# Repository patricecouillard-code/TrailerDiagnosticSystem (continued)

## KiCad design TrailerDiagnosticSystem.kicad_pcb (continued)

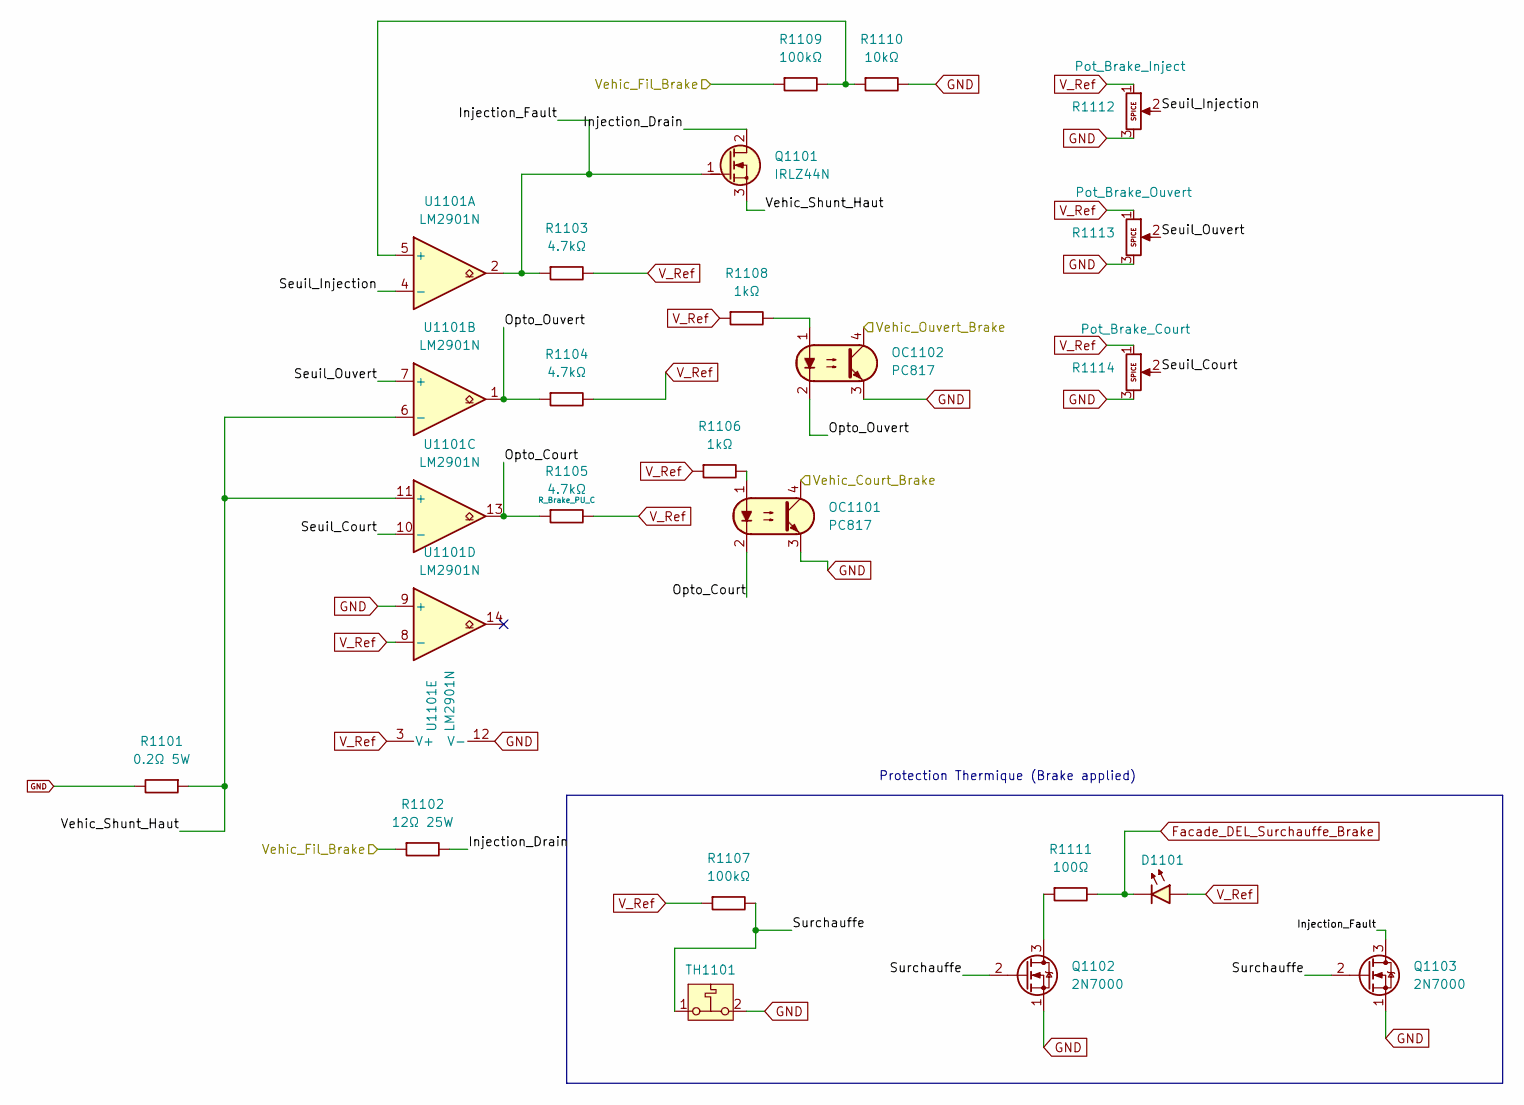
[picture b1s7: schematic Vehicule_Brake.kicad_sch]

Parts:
D1101: RGB 5mm CA (ambre); LED_D5.0mm-4_RGB_Staggered_Pins; MPN WP154A4SEJ3VBDZGW/CA
OC1101, OC1102: PC817; DIP-4_W7.62mm_LongPads
Q1101: IRLZ44N; TO-220-3_Vertical_GDS
Q1102, Q1103: 2N7000; TO-92_Inline_Wide_SGD
R1101: 0.2Ω 5W; R_Axial_Power_L25.0mm_W9.0mm_P27.94mm; MPN SQP500JB-0R2
R1102: 12Ω 25W; TerminalBlock_Phoenix_PT-1,5-2-3.5-H_1x02_P3.50mm_Horizontal; MPN HSA2512RJ
R1103, R1104, R1105: 4.7kΩ; R_Axial_DIN0207_L6.3mm_D2.5mm_P10.16mm_Horizontal
R1106, R1108: 1kΩ; R_Axial_DIN0207_L6.3mm_D2.5mm_P10.16mm_Horizontal
R1107, R1109: 100kΩ; R_Axial_DIN0207_L6.3mm_D2.5mm_P10.16mm_Horizontal
R1110: 10kΩ; R_Axial_DIN0207_L6.3mm_D2.5mm_P10.16mm_Horizontal
R1111: 100Ω; R_Axial_DIN0207_L6.3mm_D2.5mm_P10.16mm_Horizontal
R1112, R1113, R1114: 10kΩ; TRIM_3296W1103LF; MPN 3296W-1-103LF
TH1101: Thermostat 95°C NC; TerminalBlock_Phoenix_PT-1,5-2-3.5-H_1x02_P3.50mm_Horizontal; MPN CS709525Y
U1101: LM2901N; DIP-14_W7.62mm_Socket

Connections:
/Canal_Brake/Bloc_Test_Brake/Vehic_Court_Brake: OC1101.4; also elsewhere on the board
/Canal_Brake/Bloc_Test_Brake/Vehic_Ouvert_Brake: OC1102.4; also elsewhere on the board
/Canal_Brake/Vehicule_Brake/Injection_Drain: Q1101.2 (D), R1102.2
/Canal_Brake/Vehicule_Brake/Injection_Fault: Q1101.1 (G), Q1103.3 (D), R1103.1, U1101.2
/Canal_Brake/Vehicule_Brake/Opto_Court: OC1101.2, R1105.1, U1101.13
/Canal_Brake/Vehicule_Brake/Opto_Ouvert: OC1102.2, R1104.1, U1101.1
/Canal_Brake/Vehicule_Brake/Seuil_Court: R1114.2, U1101.10 (-)
/Canal_Brake/Vehicule_Brake/Seuil_Injection: R1112.2, U1101.4 (-)
/Canal_Brake/Vehicule_Brake/Seuil_Ouvert: R1113.2, U1101.7 (+)
/Canal_Brake/Vehicule_Brake/Surchauffe: Q1102.2 (G), Q1103.2 (G), R1107.2, TH1101.1
/Canal_Brake/Vehicule_Brake/Vehic_Shunt_Haut: Q1101.3 (S), R1101.1, U1101.6 (-), U1101.11 (+)
/Vehic_Fil_Brake: R1102.1, R1109.1; also elsewhere on the board
Facade_DEL_Surchauffe_Brake: D1101.1 (K), R1111.2; also elsewhere on the board
GND: OC1101.3, OC1102.3, Q1102.1 (S), Q1103.1 (S), R1101.2, R1110.2, R1112.3, R1113.3, R1114.3, TH1101.2, U1101.9 (+), U1101.12 (V-); also elsewhere on the board
unnamed: OC1101.1, R1106.2
unnamed: OC1102.1, R1108.2
unnamed: Q1102.3 (D), R1111.1
unnamed: R1109.2, R1110.1, U1101.5 (+)
V_Ref: D1101.2 (A), R1103.2, R1104.2, R1105.2, R1106.1, R1107.1, R1108.1, R1112.1, R1113.1, R1114.1, U1101.3 (V+), U1101.8 (-); also elsewhere on the board

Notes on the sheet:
Protection Thermique (Brake applied)

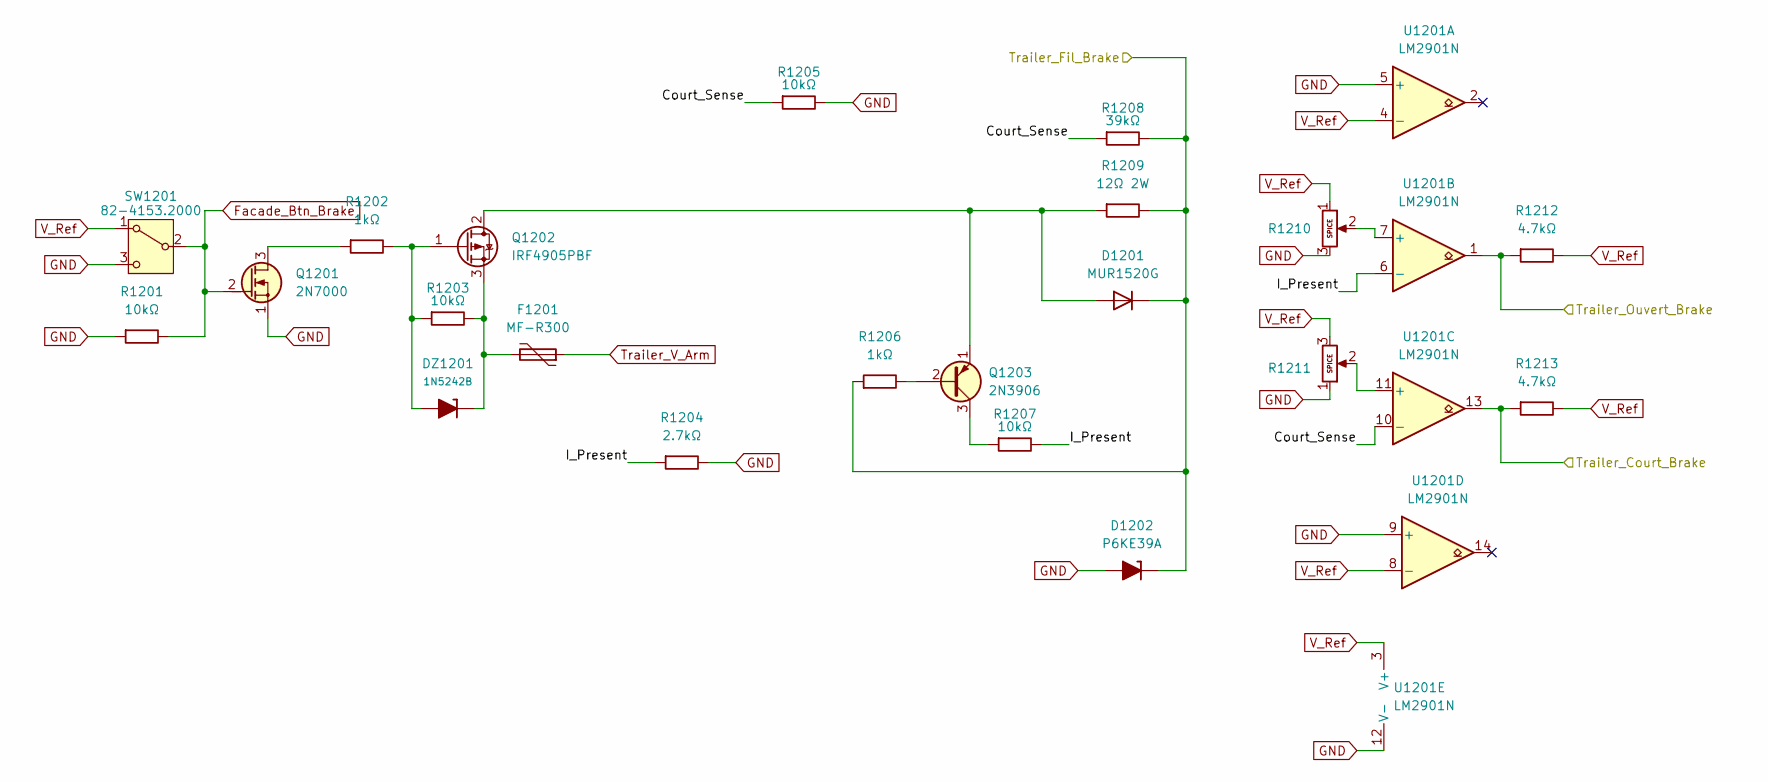
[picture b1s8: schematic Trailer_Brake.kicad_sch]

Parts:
D1201: MUR1520G; TO-220-2_Vertical
D1202: P6KE39A; D_DO-15_P10.16mm_Horizontal_Zener
DZ1201: 1N5242B; D_DO-35_SOD27_P7.62mm_Horizontal_Zener
F1201: MF-R300; PTC_Bourns_MF-R_P5.10mm_W12.0mm
Q1201: 2N7000; TO-92_Inline_Wide_SGD
Q1202: IRF4905PBF; TO-220-3_Vertical
Q1203: 2N3906; TO-92_Inline_Wide_EBC
R1201, R1203, R1205, R1207: 10kΩ; R_Axial_DIN0207_L6.3mm_D2.5mm_P10.16mm_Horizontal
R1202, R1206: 1kΩ; R_Axial_DIN0207_L6.3mm_D2.5mm_P10.16mm_Horizontal
R1204: 2.7kΩ; R_Axial_DIN0207_L6.3mm_D2.5mm_P10.16mm_Horizontal
R1208: 39kΩ; R_Axial_DIN0207_L6.3mm_D2.5mm_P10.16mm_Horizontal
R1209: 12Ω 2W; R_Axial_DIN0414_L11.9mm_D4.5mm_P15.24mm_Horizontal; MPN PR02000201209JR500
R1210, R1211: 10kΩ; TRIM_3296W1103LF; MPN 3296W-1-103LF
R1212, R1213: 4.7kΩ; R_Axial_DIN0207_L6.3mm_D2.5mm_P10.16mm_Horizontal
SW1201: 82-4153.2000
U1201: LM2901N; DIP-14_W7.62mm_Socket

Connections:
/Canal_Brake/Bloc_Test_Brake/Trailer_Court_Brake: R1213.1, U1201.13; also elsewhere on the board
/Canal_Brake/Bloc_Test_Brake/Trailer_Ouvert_Brake: R1212.1, U1201.1; also elsewhere on the board
/Canal_Brake/Trailer_Brake/Court_Sense: R1205.1, R1208.1, U1201.10 (-)
/Canal_Brake/Trailer_Brake/I_Present: R1204.1, R1207.2, U1201.6 (-)
/Trailer_Fil_Brake: D1201.1 (K), D1202.1 (K), R1206.1, R1208.2, R1209.2; also elsewhere on the board
Facade_Btn_Brake: Q1201.2 (G), R1201.2, SW1201.2 (B); also elsewhere on the board
GND: D1202.2 (A), Q1201.1 (S), R1201.1, R1204.2, R1205.2, R1210.3, R1211.1, SW1201.3 (C), U1201.5 (+), U1201.9 (+), U1201.12 (V-); also elsewhere on the board
unnamed: D1201.2 (A), Q1202.2 (D), Q1203.1 (E), R1209.1
unnamed: DZ1201.2 (A), Q1202.1 (G), R1202.2, R1203.1
unnamed: DZ1201.1 (K), F1201.2, Q1202.3 (S), R1203.2
unnamed: Q1201.3 (D), R1202.1
unnamed: Q1203.2 (B), R1206.2
unnamed: Q1203.3 (C), R1207.1
unnamed: R1210.2, U1201.7 (+)
unnamed: R1211.2, U1201.11 (+)
Trailer_V_Arm: F1201.1; also elsewhere on the board
V_Ref: R1210.1, R1211.3, R1212.2, R1213.2, SW1201.1 (A), U1201.3 (V+), U1201.4 (-), U1201.8 (-); also elsewhere on the board

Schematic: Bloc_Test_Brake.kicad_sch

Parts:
D1301, D1302, D1303, D1304, D1305, D1306, D1307, D1308, D1309, D1310, D1311, D1312, D1313, D1314, D1315, D1316, D1317, D1318, D1319, D1320, D1321, D1322, D1323: 1N4148; D_DO-35_SOD27_P7.62mm_Horizontal
D1324: RGB 5mm CA; LED_D5.0mm-4_RGB_Staggered_Pins; MPN WP154A4SEJ3VBDZGW/CA
Q1301, Q1302, Q1303, Q1304, Q1305, Q1306: 2N7000; TO-92_Inline_Wide_SGD
R1301, R1302, R1304, R1306, R1307, R1309, R1315: 4.7kΩ; R_Axial_DIN0207_L6.3mm_D2.5mm_P10.16mm_Horizontal
R1303, R1305: 100kΩ; R_Axial_DIN0207_L6.3mm_D2.5mm_P10.16mm_Horizontal
R1308, R1311, R1312: 470kΩ; R_Axial_DIN0207_L6.3mm_D2.5mm_P10.16mm_Horizontal
R1310: 150Ω; R_Axial_DIN0207_L6.3mm_D2.5mm_P10.16mm_Horizontal
R1313: 470Ω; R_Axial_DIN0207_L6.3mm_D2.5mm_P10.16mm_Horizontal
R1314: 680Ω; R_Axial_DIN0207_L6.3mm_D2.5mm_P10.16mm_Horizontal

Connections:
/Canal_Brake/Bloc_Test_Brake/Bleu: D1307.2 (A), D1308.2 (A), D1317.2 (A), D1320.2 (A), R1304.1
/Canal_Brake/Bloc_Test_Brake/Court: D1305.1 (K), D1306.1 (K), D1319.2 (A), D1321.2 (A), Q1302.2 (G), R1303.1
/Canal_Brake/Bloc_Test_Brake/Fault_Actif: D1319.1 (K), D1320.1 (K), D1323.1 (K), Q1304.2 (G), R1311.1
/Canal_Brake/Bloc_Test_Brake/Not_Btn: D1308.1 (K), Q1303.3 (D), R1309.2
/Canal_Brake/Bloc_Test_Brake/Ouvert: D1309.1 (K), D1310.1 (K), D1316.2 (A), D1322.2 (A), D1323.2 (A), R1305.2
/Canal_Brake/Bloc_Test_Brake/Ouvert_Ou_Bleu: D1316.1 (K), D1317.1 (K), Q1301.2 (G), Q1302.3 (D), R1308.1
/Canal_Brake/Bloc_Test_Brake/Trailer_Court_Actif: D1306.2 (A), D1314.2 (A), D1315.2 (A), D1318.2 (A), R1306.1
/Canal_Brake/Bloc_Test_Brake/Trailer_Court_Brake: D1314.1 (K); also elsewhere on the board
/Canal_Brake/Bloc_Test_Brake/Trailer_Ouvert_Actif: D1310.2 (A), D1311.2 (A), D1312.2 (A), D1313.2 (A), R1307.1
/Canal_Brake/Bloc_Test_Brake/Trailer_Ouvert_Brake: D1311.1 (K); also elsewhere on the board
/Canal_Brake/Bloc_Test_Brake/Vehic_Court_Actif: D1303.2 (A), D1304.2 (A), D1305.2 (A), R1302.1
/Canal_Brake/Bloc_Test_Brake/Vehic_Court_Brake: D1303.1 (K); also elsewhere on the board
/Canal_Brake/Bloc_Test_Brake/Vehic_Ouvert_Actif: D1301.2 (A), D1302.2 (A), D1309.2 (A), R1301.1
/Canal_Brake/Bloc_Test_Brake/Vehic_Ouvert_Brake: D1301.1 (K); also elsewhere on the board
/Canal_Brake/Bloc_Test_Brake/Vert_Enable: Q1304.3 (D), Q1305.2 (G), R1315.2
Facade_Brake_B: D1324.3 (BK), R1310.2; also elsewhere on the board
Facade_Brake_G: D1324.4 (GK), R1313.2; also elsewhere on the board
Facade_Brake_R: D1324.1 (RK), R1314.2; also elsewhere on the board
Facade_Btn_Brake: D1313.1 (K), D1318.1 (K), Q1303.2 (G); also elsewhere on the board
GND: Q1301.1 (S), Q1302.1 (S), Q1303.1 (S), Q1304.1 (S), Q1305.1 (S), Q1306.1 (S), R1303.2, R1305.1, R1308.2, R1311.2, R1312.1; also elsewhere on the board
Mode_Trailer: D1307.1 (K), D1312.1 (K), D1315.1 (K); also elsewhere on the board
Mode_Vehic: D1302.1 (K), D1304.1 (K); also elsewhere on the board
unnamed: D1321.1 (K), D1322.1 (K), Q1306.2 (G), R1312.2
unnamed: Q1301.3 (D), R1310.1
unnamed: Q1305.3 (D), R1313.1
unnamed: Q1306.3 (D), R1314.1
V_Ref: D1324.2 (A), R1301.2, R1302.2, R1304.2, R1306.2, R1307.2, R1309.1, R1315.1; also elsewhere on the board

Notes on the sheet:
Ouvert_V_Actif (Porte ET #3)
Court_V_Actif (Porte ET #1)
Court_T_Actif (Porte ET #2)
Rouge_Enable
Inverseur de bouton (Noeud not_btn_tail)
Court_Brake (Porte OU #1)
Ouvert_T_Actif_Brake (Porte ET #4 - 3 entrées)
Ouvert_Ou_Bleu
Ouvet_Brake (Porte OU #2)
Porte ET #5 (Bleu_Brake)

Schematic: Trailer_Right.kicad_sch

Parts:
D2001: MUR1520G; TO-220-2_Vertical
D2002: P6KE39A; D_DO-15_P10.16mm_Horizontal_Zener
DZ2001: 1N5242B; D_DO-35_SOD27_P7.62mm_Horizontal_Zener
F2001: MF-R700; PTC_Bourns_MF-R_P10.20mm_W24.2mm
Q2001: 2N7000; TO-92_Inline_Wide_SGD
Q2002: IRF4905PBF; TO-220-3_Vertical
Q2003: 2N3906; TO-92_Inline_Wide_EBC
R2001, R2003, R2005, R2007: 10kΩ; R_Axial_DIN0207_L6.3mm_D2.5mm_P10.16mm_Horizontal
R2002, R2006: 1kΩ; R_Axial_DIN0207_L6.3mm_D2.5mm_P10.16mm_Horizontal
R2004: 2.7kΩ; R_Axial_DIN0207_L6.3mm_D2.5mm_P10.16mm_Horizontal
R2008: 39kΩ; R_Axial_DIN0207_L6.3mm_D2.5mm_P10.16mm_Horizontal
R2009: 12Ω 2W; R_Axial_DIN0414_L11.9mm_D4.5mm_P15.24mm_Horizontal; MPN PR02000201209JR500
R2010, R2011: 10kΩ; TRIM_3296W1103LF; MPN 3296W-1-103LF
R2012, R2013: 4.7kΩ; R_Axial_DIN0207_L6.3mm_D2.5mm_P10.16mm_Horizontal
SW2001: 82-4153.2000
U2001: LM2901N; DIP-14_W7.62mm_Socket

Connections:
/Canal_Right/Bloc_Test_Right/Trailer_Court_Right: R2013.1, U2001.13; also elsewhere on the board
/Canal_Right/Bloc_Test_Right/Trailer_Ouvert_Right: R2012.1, U2001.1; also elsewhere on the board
/Canal_Right/Trailer_Right/Court_Sense: R2005.1, R2008.1, U2001.10 (-)
/Canal_Right/Trailer_Right/I_Present: R2004.1, R2007.2, U2001.6 (-)
/Trailer_Fil_Right: D2001.1 (K), D2002.1 (K), R2006.1, R2008.2, R2009.2; also elsewhere on the board
Facade_Btn_Right: Q2001.2 (G), R2001.2, SW2001.2 (B); also elsewhere on the board
GND: D2002.2 (A), Q2001.1 (S), R2001.1, R2004.2, R2005.2, R2010.3, R2011.1, SW2001.3 (C), U2001.5 (+), U2001.9 (+), U2001.12 (V-); also elsewhere on the board
unnamed: D2001.2 (A), Q2002.2 (D), Q2003.1 (E), R2009.1
unnamed: DZ2001.2 (A), Q2002.1 (G), R2002.2, R2003.1
unnamed: DZ2001.1 (K), F2001.2, Q2002.3 (S), R2003.2
unnamed: Q2001.3 (D), R2002.1
unnamed: Q2003.2 (B), R2006.2
unnamed: Q2003.3 (C), R2007.1
unnamed: R2010.2, U2001.7 (+)
unnamed: R2011.2, U2001.11 (+)
Trailer_V_Arm: F2001.1; also elsewhere on the board
V_Ref: R2010.1, R2011.3, R2012.2, R2013.2, SW2001.1 (A), U2001.3 (V+), U2001.4 (-), U2001.8 (-); also elsewhere on the board

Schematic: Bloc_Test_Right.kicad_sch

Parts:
D2101, D2102, D2103, D2104, D2105, D2106, D2107, D2108, D2109, D2110, D2111, D2112, D2113, D2114, D2115, D2116, D2117, D2118, D2119, D2120, D2121, D2122, D2123: 1N4148; D_DO-35_SOD27_P7.62mm_Horizontal
D2124: RGB 5mm CA; LED_D5.0mm-4_RGB_Staggered_Pins; MPN WP154A4SEJ3VBDZGW/CA
Q2101, Q2102, Q2103, Q2104, Q2105, Q2106: 2N7000; TO-92_Inline_Wide_SGD
R2101, R2104, R2107, R2108, R2110, R2111, R2112: 4.7kΩ; R_Axial_DIN0207_L6.3mm_D2.5mm_P10.16mm_Horizontal
R2102, R2105, R2109: 470kΩ; R_Axial_DIN0207_L6.3mm_D2.5mm_P10.16mm_Horizontal
R2103, R2106: 100kΩ; R_Axial_DIN0207_L6.3mm_D2.5mm_P10.16mm_Horizontal
R2113: 680Ω; R_Axial_DIN0207_L6.3mm_D2.5mm_P10.16mm_Horizontal
R2114: 470Ω; R_Axial_DIN0207_L6.3mm_D2.5mm_P10.16mm_Horizontal
R2115: 150Ω; R_Axial_DIN0207_L6.3mm_D2.5mm_P10.16mm_Horizontal

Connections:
/Canal_Right/Bloc_Test_Right/Bleu: D2104.2 (A), D2113.2 (A), D2122.2 (A), D2123.2 (A), R2112.1
/Canal_Right/Bloc_Test_Right/Court: D2109.1 (K), D2110.1 (K), D2111.2 (A), D2117.2 (A), Q2101.2 (G), R2106.2
/Canal_Right/Bloc_Test_Right/Fault_Actif: D2111.1 (K), D2112.1 (K), D2113.1 (K), Q2102.2 (G), R2105.1
/Canal_Right/Bloc_Test_Right/Not_Btn: D2123.1 (K), Q2103.3 (D), R2111.2
/Canal_Right/Bloc_Test_Right/Ouvert: D2103.2 (A), D2105.1 (K), D2106.1 (K), D2112.2 (A), D2118.2 (A), R2103.2
/Canal_Right/Bloc_Test_Right/Ouvert_Ou_Bleu: D2103.1 (K), D2104.1 (K), Q2101.3 (D), Q2106.2 (G), R2102.2
/Canal_Right/Bloc_Test_Right/Rouge_Enable: D2117.1 (K), D2118.1 (K), Q2104.2 (G), R2109.2
/Canal_Right/Bloc_Test_Right/Trailer_Court_Actif: D2107.2 (A), D2108.2 (A), D2110.2 (A), D2116.2 (A), R2104.1
/Canal_Right/Bloc_Test_Right/Trailer_Court_Right: D2107.1 (K); also elsewhere on the board
/Canal_Right/Bloc_Test_Right/Trailer_Ouvert_Actif: D2106.2 (A), D2119.2 (A), D2120.2 (A), D2121.2 (A), R2110.1
/Canal_Right/Bloc_Test_Right/Trailer_Ouvert_Right: D2119.1 (K); also elsewhere on the board
/Canal_Right/Bloc_Test_Right/Vehic_Court_Actif: D2101.2 (A), D2102.2 (A), D2109.2 (A), R2101.1
/Canal_Right/Bloc_Test_Right/Vehic_Court_Right: D2101.1 (K); also elsewhere on the board
/Canal_Right/Bloc_Test_Right/Vehic_Ouvert_Actif: D2105.2 (A), D2114.2 (A), D2115.2 (A), R2108.1
/Canal_Right/Bloc_Test_Right/Vehic_Ouvert_Right: D2114.1 (K); also elsewhere on the board
/Canal_Right/Bloc_Test_Right/Vert_Enable: Q2102.3 (D), Q2105.2 (G), R2107.2
Facade_Btn_Right: D2116.1 (K), D2121.1 (K), Q2103.2 (G); also elsewhere on the board
Facade_Right_B: D2124.3 (BK), R2115.2; also elsewhere on the board
Facade_Right_G: D2124.4 (GK), R2114.2; also elsewhere on the board
Facade_Right_R: D2124.1 (RK), R2113.2; also elsewhere on the board
GND: Q2101.1 (S), Q2102.1 (S), Q2103.1 (S), Q2104.1 (S), Q2105.1 (S), Q2106.1 (S), R2102.1, R2103.1, R2105.2, R2106.1, R2109.1; also elsewhere on the board
Mode_Trailer: D2108.1 (K), D2120.1 (K), D2122.1 (K); also elsewhere on the board
Mode_Vehic: D2102.1 (K), D2115.1 (K); also elsewhere on the board
unnamed: Q2104.3 (D), R2113.1
unnamed: Q2105.3 (D), R2114.1
unnamed: Q2106.3 (D), R2115.1
V_Ref: D2124.2 (A), R2101.2, R2104.2, R2107.1, R2108.2, R2110.2, R2111.1, R2112.2; also elsewhere on the board

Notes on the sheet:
========================================================================== NIVEAU 1 ==========================================================================
Porte OU Fault_Actif_Right (3 entrées) + inverseur vert
3ième Porte "ET" (Ouvert_V_Actif_Right)
=========================================== NIVEAU 2 =================================================
1ère Porte "OU" (Ouvert_Right)
2ième Porte "OU" (Court_Right)
1ère Porte "ET" (Court_V_Actif_Right)
Porte OU Rouge_Enable_Right
4ième Porte "ET" (Ouvert_T_Actif_Right)
Inverseur (Dépendance de Bleu_Right)
2ième Porte "ET" (Court_T_Actif_Right)
5ième Porte "ET" (Bleu_Right)
====================================== NIVEAU 3 ==================
Porte OU Ouvert_Ou_Bleu_Right + override

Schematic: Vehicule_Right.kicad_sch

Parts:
OC1901, OC1902: PC817; DIP-4_W7.62mm_LongPads
Q1901: IRLZ44N; TO-220-3_Vertical_GDS
R1901: 12Ω 25W; TerminalBlock_Phoenix_PT-1,5-2-3.5-H_1x02_P3.50mm_Horizontal; MPN HSA2512RJ
R1902: 0.2Ω 5W; R_Axial_Power_L25.0mm_W9.0mm_P27.94mm; MPN SQP500JB-0R2
R1903, R1904, R1905: 4.7kΩ; R_Axial_DIN0207_L6.3mm_D2.5mm_P10.16mm_Horizontal
R1906, R1907: 1kΩ; R_Axial_DIN0207_L6.3mm_D2.5mm_P10.16mm_Horizontal
R1908: 100kΩ; R_Axial_DIN0207_L6.3mm_D2.5mm_P10.16mm_Horizontal
R1909: 10kΩ; R_Axial_DIN0207_L6.3mm_D2.5mm_P10.16mm_Horizontal
R1910, R1911, R1912: 10kΩ; TRIM_3296W1103LF; MPN 3296W-1-103LF
U1901: LM2901N; DIP-14_W7.62mm_Socket

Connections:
/Canal_Right/Bloc_Test_Right/Vehic_Court_Right: OC1901.4; also elsewhere on the board
/Canal_Right/Bloc_Test_Right/Vehic_Ouvert_Right: OC1902.4; also elsewhere on the board
/Canal_Right/Vehicule_Right/Injection_Drain: Q1901.2 (D), R1901.2
/Canal_Right/Vehicule_Right/Injection_Fault: Q1901.1 (G), R1903.1, U1901.2
/Canal_Right/Vehicule_Right/Opto_Court: OC1901.2, R1905.1, U1901.13
/Canal_Right/Vehicule_Right/Opto_Ouvert: OC1902.2, R1904.1, U1901.1
/Canal_Right/Vehicule_Right/Seuil_Court: R1912.2, U1901.10 (-)
/Canal_Right/Vehicule_Right/Seuil_Injection: R1910.2, U1901.4 (-)
/Canal_Right/Vehicule_Right/Seuil_Ouvert: R1911.2, U1901.7 (+)
/Canal_Right/Vehicule_Right/Vehic_Shunt_Haut: Q1901.3 (S), R1902.1, U1901.6 (-), U1901.11 (+)
/Vehic_Fil_Right: R1901.1, R1908.1; also elsewhere on the board
GND: OC1901.3, OC1902.3, R1902.2, R1909.2, R1910.3, R1911.3, R1912.3, U1901.9 (+), U1901.12 (V-); also elsewhere on the board
unnamed: OC1901.1, R1906.2
unnamed: OC1902.1, R1907.2
unnamed: R1908.2, R1909.1, U1901.5 (+)
V_Ref: R1903.2, R1904.2, R1905.2, R1906.1, R1907.1, R1910.1, R1911.1, R1912.1, U1901.3 (V+), U1901.8 (-); also elsewhere on the board

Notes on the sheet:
Non_Utilisé
Court-circuit
Ouvvert
Right_Vehic_Shunt_Haut
Injection

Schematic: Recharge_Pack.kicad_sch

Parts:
C401: 2.2µF 50V; CAPRB500W50L450T300H550; MPN FG24X7R1H225KRT06
D401: RGB 5mm CA (bleu); MPN WP154A4SEJ3VBDZGW/CA
J401: EN3P2MX
J402: Micro-Fit 3.0 1x06; Molex_Micro-Fit_3.0_43650-0615_1x06_P3.00mm_Vertical
Q401: IRLZ44N; TO-220-3_Vertical_GDS
R401: 470Ω 1W; R_Axial_DIN0309_L9.0mm_D3.2mm_P12.70mm_Horizontal; MPN PR01000104700JR500
R402: 330Ω; R_Axial_DIN0207_L6.3mm_D2.5mm_P10.16mm_Horizontal
TH401: Thermostat NO 15°C; MPN CS701515Y
U401: LM74610QDGKRQ1; SOP65P490X110-8N; PARTREV B

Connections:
/Alimentation/Batt_Interne_Pos: Q401.2 (D), U401.8 (CATHODE); also elsewhere on the board
/Alimentation/Batt_Neg: J401.2, J402.2, R401.1; also elsewhere on the board
/Alimentation/Recharge_Pack/Recharge_DEL_A: D401.2 (A), J402.5, R402.2
/Alimentation/Recharge_Pack/Recharge_Pos: J401.1, J402.1, J402.3, R402.1, TH401.1 (A)
/Alimentation/Recharge_Pack/Recharge_Therm: D401.1 (K), J402.4, J402.6, Q401.3 (S), R401.2, TH401.2 (B), U401.4 (ANODE)
unnamed: Q401.1 (G), U401.2 (GATE_PULL_DOWN), U401.6 (GATE_DRIVE)
unnamed: C401.1, U401.7 (VCAPH)
unnamed: C401.2, U401.1 (VCAPL)

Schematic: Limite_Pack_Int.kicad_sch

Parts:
C301: 4.7µF 63V; C_Rect_L19.0mm_W7.0mm_P15.00mm_MKS4; MPN MKS4C044704D00KSSD 10%
C302, C303: 10nF 50V; CAPRR254W50L508T317H508; MPN C315C103K5R5TA
D301: RGB 5mm CA (ambre); LED_D5.0mm-4_RGB_Staggered_Pins; MPN WP154A4SEJ3VBDZGW/CA
Q301, Q303: 2N3906; TO-92_Inline_Wide_EBC
Q302: 2N3904; TO-92_Inline_Wide_EBC
Q304: 2N7000; TO-92_Inline_Wide_SGD
R301: 1.5kΩ; R_Axial_DIN0207_L6.3mm_D2.5mm_P10.16mm_Horizontal
R302, R303, R309, R312: 100kΩ; R_Axial_DIN0207_L6.3mm_D2.5mm_P10.16mm_Horizontal
R304: 1kΩ; TRIM_3296W-1-102LF; MPN 3296W-1-102LF
R305: 1kΩ; R_Axial_DIN0207_L6.3mm_D2.5mm_P10.16mm_Horizontal
R306: 18kΩ; R_Axial_DIN0207_L6.3mm_D2.5mm_P10.16mm_Horizontal
R307: 39kΩ; R_Axial_DIN0207_L6.3mm_D2.5mm_P10.16mm_Horizontal
R308, R310: 10kΩ; R_Axial_DIN0207_L6.3mm_D2.5mm_P10.16mm_Horizontal
R311: 1.8kΩ; R_Axial_DIN0207_L6.3mm_D2.5mm_P10.16mm_Horizontal

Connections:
/Alimentation/Batt_Interne_Pos: Q301.1 (E), R301.1; also elsewhere on the board
/Alimentation/Batt_Interne_Shunt: R304.3; also elsewhere on the board
/Alimentation/Bus_CutOff_Gate: Q304.3 (D); also elsewhere on the board
/Alimentation/Limite_Pack_Int/Batt_Ext_Requise: Q303.3 (C), R307.2, R310.1, R311.1
/Alimentation/Limite_Pack_Int/Mesure_Courant_Pack: Q301.2 (B), R305.2
/Alimentation/V_Int_Actif: C303.2, Q303.1 (E), R309.2; also elsewhere on the board
Facade_DEL_Batt_Ext: D301.2 (A), R311.2; also elsewhere on the board
GND: C301.2, C302.1, D301.1 (K), Q302.1 (E), Q304.1 (S), R306.2, R312.2; also elsewhere on the board
unnamed: C301.1, R302.2, R303.1
unnamed: Q301.3 (C), R302.1
unnamed: C302.2, Q302.2 (B), R303.2, R306.1, R307.1
unnamed: Q302.3 (C), R308.1
unnamed: C303.1, Q303.2 (B), R308.2, R309.1
unnamed: Q304.2 (G), R310.2, R312.1
unnamed: R301.2, R304.1
unnamed: R304.2, R305.1

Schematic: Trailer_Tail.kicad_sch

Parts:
D801: MUR1520G; TO-220-2_Vertical
D802: P6KE39A; D_DO-15_P10.16mm_Horizontal_Zener
DZ801: 1N5242B; D_DO-35_SOD27_P7.62mm_Horizontal_Zener
F801: MF-R800; PTC_Bourns_MF-R_P10.20mm_W24.2mm
Q801: 2N7000; TO-92_Inline_Wide_SGD
Q802: IRF4905PBF; TO-220-3_Vertical
Q803: 2N3906; TO-92_Inline_Wide_EBC
R801, R803, R805, R807: 10kΩ; R_Axial_DIN0207_L6.3mm_D2.5mm_P10.16mm_Horizontal
R802, R806: 1kΩ; R_Axial_DIN0207_L6.3mm_D2.5mm_P10.16mm_Horizontal
R804: 2.7kΩ; R_Axial_DIN0207_L6.3mm_D2.5mm_P10.16mm_Horizontal
R808: 39kΩ; R_Axial_DIN0207_L6.3mm_D2.5mm_P10.16mm_Horizontal
R809: 12Ω 2W; R_Axial_DIN0414_L11.9mm_D4.5mm_P15.24mm_Horizontal; MPN PR02000201209JR500
R810, R811: 10kΩ; TRIM_3296W1103LF; MPN 3296W-1-103LF
R812, R813: 4.7kΩ; R_Axial_DIN0207_L6.3mm_D2.5mm_P10.16mm_Horizontal
SW801: 82-4153.2000
U801: LM2901N; DIP-14_W7.62mm_Socket

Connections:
/Canal_Tail/Bloc_Test_Tail/Trailer_Court_Tail: R813.1, U801.13; also elsewhere on the board
/Canal_Tail/Bloc_Test_Tail/Trailer_Ouvert_Tail: R812.1, U801.1; also elsewhere on the board
/Canal_Tail/Trailer_Tail/Court_Sense: R805.1, R808.1, U801.10 (-)
/Canal_Tail/Trailer_Tail/I_Present: R804.1, R807.2, U801.6 (-)
/Trailer_Fil_Tail: D801.1 (K), D802.1 (K), R806.1, R808.2, R809.2; also elsewhere on the board
Facade_Btn_Tail: Q801.2 (G), R801.2, SW801.2 (B); also elsewhere on the board
GND: D802.2 (A), Q801.1 (S), R801.1, R804.2, R805.2, R810.3, R811.1, SW801.3 (C), U801.5 (+), U801.9 (+), U801.12 (V-); also elsewhere on the board
unnamed: D801.2 (A), Q802.2 (D), Q803.1 (E), R809.1
unnamed: DZ801.2 (A), Q802.1 (G), R802.2, R803.1
unnamed: DZ801.1 (K), F801.2, Q802.3 (S), R803.2
unnamed: Q801.3 (D), R802.1
unnamed: Q803.2 (B), R806.2
unnamed: Q803.3 (C), R807.1
unnamed: R810.2, U801.7 (+)
unnamed: R811.2, U801.11 (+)
Trailer_V_Arm: F801.1; also elsewhere on the board
V_Ref: R810.1, R811.3, R812.2, R813.2, SW801.1 (A), U801.3 (V+), U801.4 (-), U801.8 (-); also elsewhere on the board

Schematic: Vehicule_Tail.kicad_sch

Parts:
OC701, OC702: PC817; DIP-4_W7.62mm_LongPads
Q701: IRLZ44N; TO-220-3_Vertical_GDS
R701: 12Ω 25W; TerminalBlock_Phoenix_PT-1,5-2-3.5-H_1x02_P3.50mm_Horizontal; MPN HSA2512RJ
R702: 0.2Ω 5W; R_Axial_Power_L25.0mm_W9.0mm_P27.94mm; MPN SQP500JB-0R2
R703, R704, R705: 4.7kΩ; R_Axial_DIN0207_L6.3mm_D2.5mm_P10.16mm_Horizontal
R706, R707: 1kΩ; R_Axial_DIN0207_L6.3mm_D2.5mm_P10.16mm_Horizontal
R708: 100kΩ; R_Axial_DIN0207_L6.3mm_D2.5mm_P10.16mm_Horizontal
R709: 10kΩ; R_Axial_DIN0207_L6.3mm_D2.5mm_P10.16mm_Horizontal
R710, R711, R712: 10kΩ; TRIM_3296W1103LF; MPN 3296W-1-103LF
U701: LM2901N; DIP-14_W7.62mm_Socket

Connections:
/Canal_Tail/Bloc_Test_Tail/Vehic_Court_Tail: OC701.4; also elsewhere on the board
/Canal_Tail/Bloc_Test_Tail/Vehic_Ouvert_Tail: OC702.4; also elsewhere on the board
/Canal_Tail/Vehicule_Tail/Injection_Drain: Q701.2 (D), R701.2
/Canal_Tail/Vehicule_Tail/Injection_Fault: Q701.1 (G), R703.1, U701.2
/Canal_Tail/Vehicule_Tail/Seuil_Court: R712.2, U701.10 (-)
/Canal_Tail/Vehicule_Tail/Seuil_Injection: R710.2, U701.4 (-)
/Canal_Tail/Vehicule_Tail/Seuil_Ouvert: R711.2, U701.7 (+)
/Canal_Tail/Vehicule_Tail/Vehic_Shunt_Haut: Q701.3 (S), R702.1, U701.6 (-), U701.11 (+)
/Vehic_Fil_Tail: R701.1, R708.1; also elsewhere on the board
GND: OC701.3, OC702.3, R702.2, R709.2, R710.3, R711.3, R712.3, U701.9 (+), U701.12 (V-); also elsewhere on the board
unnamed: OC701.1, R706.2
unnamed: OC701.2, R705.1, U701.13
unnamed: OC702.1, R707.2
unnamed: OC702.2, R704.1, U701.1
unnamed: R708.2, R709.1, U701.5 (+)
V_Ref: R703.2, R704.2, R705.2, R706.1, R707.1, R710.1, R711.1, R712.1, U701.3 (V+), U701.8 (-); also elsewhere on the board

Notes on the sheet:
Injection
Ouvvert
Court-circuit
Non_Utilisé

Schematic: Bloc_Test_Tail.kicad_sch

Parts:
D901, D902, D903, D904, D905, D906, D907, D908, D909, D910, D911, D912, D913, D914, D915, D916, D917, D918, D919, D920, D921, D922, D923: 1N4148; D_DO-35_SOD27_P7.62mm_Horizontal
D924: RGB 5mm CA; LED_D5.0mm-4_RGB_Staggered_Pins; MPN WP154A4SEJ3VBDZGW/CA
Q901, Q902, Q903, Q904, Q905, Q906: 2N7000; TO-92_Inline_Wide_SGD
R901, R902, R904, R905, R906, R909, R915: 4.7kΩ; R_Axial_DIN0207_L6.3mm_D2.5mm_P10.16mm_Horizontal
R903, R907: 100kΩ; R_Axial_DIN0207_L6.3mm_D2.5mm_P10.16mm_Horizontal
R908, R911, R913: 470kΩ; R_Axial_DIN0207_L6.3mm_D2.5mm_P10.16mm_Horizontal
R910: 150Ω; R_Axial_DIN0207_L6.3mm_D2.5mm_P10.16mm_Horizontal
R912: 470Ω; R_Axial_DIN0207_L6.3mm_D2.5mm_P10.16mm_Horizontal
R914: 680Ω; R_Axial_DIN0207_L6.3mm_D2.5mm_P10.16mm_Horizontal

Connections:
/Canal_Tail/Bloc_Test_Tail/Bleu: D907.2 (A), D908.2 (A), D918.2 (A), D920.2 (A), R904.1
/Canal_Tail/Bloc_Test_Tail/Court: D905.1 (K), D906.1 (K), D919.2 (A), D921.2 (A), Q902.2 (G), R903.1
/Canal_Tail/Bloc_Test_Tail/Fault_Actif: D919.1 (K), D920.1 (K), D923.1 (K), Q905.2 (G), R911.1
/Canal_Tail/Bloc_Test_Tail/Not_Btn: D908.1 (K), Q903.3 (D), R909.2
/Canal_Tail/Bloc_Test_Tail/Ouvert: D915.1 (K), D916.1 (K), D917.2 (A), D922.2 (A), D923.2 (A), R907.2
/Canal_Tail/Bloc_Test_Tail/Ouvert_Ou_Bleu: D917.1 (K), D918.1 (K), Q901.2 (G), Q902.3 (D), R908.1
/Canal_Tail/Bloc_Test_Tail/Trailer_Court_Actif: D906.2 (A), D912.2 (A), D913.2 (A), D914.2 (A), R906.1
/Canal_Tail/Bloc_Test_Tail/Trailer_Court_Tail: D912.1 (K); also elsewhere on the board
/Canal_Tail/Bloc_Test_Tail/Trailer_Ouvert_Actif: D909.2 (A), D910.2 (A), D911.2 (A), D916.2 (A), R905.1
/Canal_Tail/Bloc_Test_Tail/Trailer_Ouvert_Tail: D909.1 (K); also elsewhere on the board
/Canal_Tail/Bloc_Test_Tail/Vehic_Court_Actif: D903.2 (A), D904.2 (A), D905.2 (A), R902.1
/Canal_Tail/Bloc_Test_Tail/Vehic_Court_Tail: D903.1 (K); also elsewhere on the board
/Canal_Tail/Bloc_Test_Tail/Vehic_Ouvert_Actif: D901.2 (A), D902.2 (A), D915.2 (A), R901.1
/Canal_Tail/Bloc_Test_Tail/Vehic_Ouvert_Tail: D901.1 (K); also elsewhere on the board
/Canal_Tail/Bloc_Test_Tail/Vert_Enable: Q904.2 (G), Q905.3 (D), R915.2
Facade_Btn_Tail: D911.1 (K), D914.1 (K), Q903.2 (G); also elsewhere on the board
Facade_Tail_B: D924.3 (BK), R910.2; also elsewhere on the board
Facade_Tail_G: D924.4 (GK), R912.2; also elsewhere on the board
Facade_Tail_R: D924.1 (RK), R914.2; also elsewhere on the board
GND: Q901.1 (S), Q902.1 (S), Q903.1 (S), Q904.1 (S), Q905.1 (S), Q906.1 (S), R903.2, R907.1, R908.2, R911.2, R913.1; also elsewhere on the board
Mode_Trailer: D907.1 (K), D910.1 (K), D913.1 (K); also elsewhere on the board
Mode_Vehic: D902.1 (K), D904.1 (K); also elsewhere on the board
unnamed: D921.1 (K), D922.1 (K), Q906.2 (G), R913.2
unnamed: Q901.3 (D), R910.1
unnamed: Q904.3 (D), R912.1
unnamed: Q906.3 (D), R914.1
V_Ref: D924.2 (A), R901.2, R902.2, R904.2, R905.2, R906.2, R909.1, R915.1; also elsewhere on the board

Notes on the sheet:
Ouvert_V_Actif (Porte ET #3)
Ouvert_Ou_Bleu
Court_T_Actif (Porte ET #2)
Ouvet_Tail (Porte OU #2)
Ouvert_T_Actif (Porte ET #4 - 3 entrées)
Court_Tail (Porte OU #1)
Rouge_Enable
Court_V_Actif (Porte ET #1)
Porte ET #5 (Bleu_Tail)
Inverseur de bouton (Noeud not_btn_tail)
Fault_Actif

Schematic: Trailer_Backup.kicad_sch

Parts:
D2401: MUR1520G; TO-220-2_Vertical
D2402: P6KE39A; D_DO-15_P10.16mm_Horizontal_Zener
DZ2401: 1N5242B; D_DO-35_SOD27_P7.62mm_Horizontal_Zener
F2401: MF-R700; PTC_Bourns_MF-R_P10.20mm_W24.2mm
Q2401: 2N7000; TO-92_Inline_Wide_SGD
Q2402: IRF4905PBF; TO-220-3_Vertical
Q2403: 2N3906; TO-92_Inline_Wide_EBC
R2401, R2403, R2405, R2407: 10kΩ; R_Axial_DIN0207_L6.3mm_D2.5mm_P10.16mm_Horizontal
R2402, R2406: 1kΩ; R_Axial_DIN0207_L6.3mm_D2.5mm_P10.16mm_Horizontal
R2404: 2.7kΩ; R_Axial_DIN0207_L6.3mm_D2.5mm_P10.16mm_Horizontal
R2408: 39kΩ; R_Axial_DIN0207_L6.3mm_D2.5mm_P10.16mm_Horizontal
R2409: 12Ω 2W; R_Axial_DIN0414_L11.9mm_D4.5mm_P15.24mm_Horizontal; MPN PR02000201209JR500
R2410, R2411: 10kΩ; TRIM_3296W1103LF; MPN 3296W-1-103LF
R2412, R2413: 4.7kΩ; R_Axial_DIN0207_L6.3mm_D2.5mm_P10.16mm_Horizontal
SW2401: 82-4153.2000
U2401: LM2901N; DIP-14_W7.62mm_Socket

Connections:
/Canal_Backup/Bloc_Test_Backup/Trailer_Court_Backup: R2413.1, U2401.13; also elsewhere on the board
/Canal_Backup/Bloc_Test_Backup/Trailer_Ouvert_Backup: R2412.1, U2401.1; also elsewhere on the board
/Canal_Backup/Trailer_Backup/Court_Sense: R2405.1, R2408.1, U2401.10 (-)
/Canal_Backup/Trailer_Backup/I_Present: R2404.1, R2407.2, U2401.6 (-)
/Trailer_Fil_Backup: D2401.1 (K), D2402.1 (K), R2406.1, R2408.2, R2409.2; also elsewhere on the board
Facade_Btn_Backup: Q2401.2 (G), R2401.2, SW2401.2 (B); also elsewhere on the board
GND: D2402.2 (A), Q2401.1 (S), R2401.1, R2404.2, R2405.2, R2410.3, R2411.1, SW2401.3 (C), U2401.5 (+), U2401.9 (+), U2401.12 (V-); also elsewhere on the board
unnamed: D2401.2 (A), Q2402.2 (D), Q2403.1 (E), R2409.1
unnamed: DZ2401.2 (A), Q2402.1 (G), R2402.2, R2403.1
unnamed: DZ2401.1 (K), F2401.2, Q2402.3 (S), R2403.2
unnamed: Q2401.3 (D), R2402.1
unnamed: Q2403.2 (B), R2406.2
unnamed: Q2403.3 (C), R2407.1
unnamed: R2410.2, U2401.7 (+)
unnamed: R2411.2, U2401.11 (+)
Trailer_V_Arm: F2401.1; also elsewhere on the board
V_Ref: R2410.1, R2411.3, R2412.2, R2413.2, SW2401.1 (A), U2401.3 (V+), U2401.4 (-), U2401.8 (-); also elsewhere on the board

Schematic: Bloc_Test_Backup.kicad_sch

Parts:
D2501, D2502, D2503, D2504, D2505, D2506, D2507, D2508, D2509, D2510, D2511, D2512, D2513, D2514, D2515, D2516, D2517, D2518, D2519, D2520, D2521, D2522, D2523: 1N4148; D_DO-35_SOD27_P7.62mm_Horizontal
D2524: RGB 5mm CA; LED_D5.0mm-4_RGB_Staggered_Pins; MPN WP154A4SEJ3VBDZGW/CA
Q2501, Q2502, Q2503, Q2504, Q2505, Q2506: 2N7000; TO-92_Inline_Wide_SGD
R2501, R2504, R2507, R2508, R2510, R2511, R2512: 4.7kΩ; R_Axial_DIN0207_L6.3mm_D2.5mm_P10.16mm_Horizontal
R2502, R2505, R2509: 470kΩ; R_Axial_DIN0207_L6.3mm_D2.5mm_P10.16mm_Horizontal
R2503, R2506: 100kΩ; R_Axial_DIN0207_L6.3mm_D2.5mm_P10.16mm_Horizontal
R2513: 680Ω; R_Axial_DIN0207_L6.3mm_D2.5mm_P10.16mm_Horizontal
R2514: 470Ω; R_Axial_DIN0207_L6.3mm_D2.5mm_P10.16mm_Horizontal
R2515: 150Ω; R_Axial_DIN0207_L6.3mm_D2.5mm_P10.16mm_Horizontal

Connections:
/Canal_Backup/Bloc_Test_Backup/Bleu: D2504.2 (A), D2513.2 (A), D2522.2 (A), D2523.2 (A), R2512.1
/Canal_Backup/Bloc_Test_Backup/Court: D2509.1 (K), D2510.1 (K), D2511.2 (A), D2517.2 (A), Q2501.2 (G), R2506.2
/Canal_Backup/Bloc_Test_Backup/Fault_Actif: D2511.1 (K), D2512.1 (K), D2513.1 (K), Q2502.2 (G), R2505.1
/Canal_Backup/Bloc_Test_Backup/Not_Btn: D2523.1 (K), Q2503.3 (D), R2511.2
/Canal_Backup/Bloc_Test_Backup/Ouvert: D2503.2 (A), D2505.1 (K), D2506.1 (K), D2512.2 (A), D2518.2 (A), R2503.2
/Canal_Backup/Bloc_Test_Backup/Ouvert_Ou_Bleu: D2503.1 (K), D2504.1 (K), Q2501.3 (D), Q2506.2 (G), R2502.2
/Canal_Backup/Bloc_Test_Backup/Rouge_Enable: D2517.1 (K), D2518.1 (K), Q2504.2 (G), R2509.2
/Canal_Backup/Bloc_Test_Backup/Trailer_Court_Actif: D2507.2 (A), D2508.2 (A), D2510.2 (A), D2516.2 (A), R2504.1
/Canal_Backup/Bloc_Test_Backup/Trailer_Court_Backup: D2507.1 (K); also elsewhere on the board
/Canal_Backup/Bloc_Test_Backup/Trailer_Ouvert_Actif: D2506.2 (A), D2519.2 (A), D2520.2 (A), D2521.2 (A), R2510.1
/Canal_Backup/Bloc_Test_Backup/Trailer_Ouvert_Backup: D2519.1 (K); also elsewhere on the board
/Canal_Backup/Bloc_Test_Backup/Vehic_Court_Actif: D2501.2 (A), D2502.2 (A), D2509.2 (A), R2501.1
/Canal_Backup/Bloc_Test_Backup/Vehic_Court_Backup: D2501.1 (K); also elsewhere on the board
/Canal_Backup/Bloc_Test_Backup/Vehic_Ouvert_Actif: D2505.2 (A), D2514.2 (A), D2515.2 (A), R2508.1
/Canal_Backup/Bloc_Test_Backup/Vehic_Ouvert_Backup: D2514.1 (K); also elsewhere on the board
/Canal_Backup/Bloc_Test_Backup/Vert_Enable: Q2502.3 (D), Q2505.2 (G), R2507.2
Facade_Backup_B: D2524.3 (BK), R2515.2; also elsewhere on the board
Facade_Backup_G: D2524.4 (GK), R2514.2; also elsewhere on the board
Facade_Backup_R: D2524.1 (RK), R2513.2; also elsewhere on the board
Facade_Btn_Backup: D2516.1 (K), D2521.1 (K), Q2503.2 (G); also elsewhere on the board
GND: Q2501.1 (S), Q2502.1 (S), Q2503.1 (S), Q2504.1 (S), Q2505.1 (S), Q2506.1 (S), R2502.1, R2503.1, R2505.2, R2506.1, R2509.1; also elsewhere on the board
Mode_Trailer: D2508.1 (K), D2520.1 (K), D2522.1 (K); also elsewhere on the board
Mode_Vehic: D2502.1 (K), D2515.1 (K); also elsewhere on the board
unnamed: Q2504.3 (D), R2513.1
unnamed: Q2505.3 (D), R2514.1
unnamed: Q2506.3 (D), R2515.1
V_Ref: D2524.2 (A), R2501.2, R2504.2, R2507.1, R2508.2, R2510.2, R2511.1, R2512.2; also elsewhere on the board

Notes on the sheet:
========================================================================== NIVEAU 1 ==========================================================================
Inverseur (Dépendance de Bleu_Backup)
====================================== NIVEAU 3 ==================
2ième Porte "OU" (Court_Backup)
Porte OU Ouvert_Ou_Bleu_Backup + override
Porte OU Fault_Actif_Backup (3 entrées) + inverseur vert
1ère Porte "ET" (Court_V_Actif_Backup)
Porte OU Rouge_Enable_Backup
3ième Porte "ET" (Ouvert_V_Actif_Backup)
4ième Porte "ET" (Ouvert_T_Actif_Backup)
5ième Porte "ET" (Bleu_Backup)
1ère Porte "OU" (Ouvert_Backup)
=========================================== NIVEAU 2 =================================================
2ième Porte "ET" (Court_T_Actif_Backup)

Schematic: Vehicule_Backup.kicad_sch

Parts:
OC2301, OC2302: PC817; DIP-4_W7.62mm_LongPads
Q2301: IRLZ44N; TO-220-3_Vertical_GDS
R2301: 0.2Ω 5W; R_Axial_Power_L25.0mm_W9.0mm_P27.94mm; MPN SQP500JB-0R2
R2302: 12Ω 25W; TerminalBlock_Phoenix_PT-1,5-2-3.5-H_1x02_P3.50mm_Horizontal; MPN HSA2512RJ
R2303, R2304, R2305: 4.7kΩ; R_Axial_DIN0207_L6.3mm_D2.5mm_P10.16mm_Horizontal
R2306: 100kΩ; R_Axial_DIN0207_L6.3mm_D2.5mm_P10.16mm_Horizontal
R2307: 10kΩ; R_Axial_DIN0207_L6.3mm_D2.5mm_P10.16mm_Horizontal
R2308, R2309: 1kΩ; R_Axial_DIN0207_L6.3mm_D2.5mm_P10.16mm_Horizontal
R2310, R2311, R2312: 10kΩ; TRIM_3296W1103LF; MPN 3296W-1-103LF
U2301: LM2901N; DIP-14_W7.62mm_Socket

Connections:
/Canal_Backup/Bloc_Test_Backup/Vehic_Court_Backup: OC2302.4; also elsewhere on the board
/Canal_Backup/Bloc_Test_Backup/Vehic_Ouvert_Backup: OC2301.4; also elsewhere on the board
/Canal_Backup/Vehicule_Backup/Injection_Drain: Q2301.2 (D), R2302.2
/Canal_Backup/Vehicule_Backup/Injection_Fault: Q2301.1 (G), R2303.1, U2301.2
/Canal_Backup/Vehicule_Backup/Opto_Court: OC2302.2, R2305.1, U2301.13
/Canal_Backup/Vehicule_Backup/Opto_Ouvert: OC2301.2, R2304.1, U2301.1
/Canal_Backup/Vehicule_Backup/Seuil_Court: R2312.2, U2301.10 (-)
/Canal_Backup/Vehicule_Backup/Seuil_Injection: R2310.2, U2301.4 (-)
/Canal_Backup/Vehicule_Backup/Seuil_Ouvert: R2311.2, U2301.7 (+)
/Canal_Backup/Vehicule_Backup/Vehic_Shunt_Haut: Q2301.3 (S), R2301.1, U2301.6 (-), U2301.11 (+)
/Vehic_Fil_Backup: R2302.1, R2306.1; also elsewhere on the board
GND: OC2301.3, OC2302.3, R2301.2, R2307.2, R2310.3, R2311.3, R2312.3, U2301.9 (+), U2301.12 (V-); also elsewhere on the board
unnamed: OC2301.1, R2308.2
unnamed: OC2302.1, R2309.2
unnamed: R2306.2, R2307.1, U2301.5 (+)
V_Ref: R2303.2, R2304.2, R2305.2, R2308.1, R2309.1, R2310.1, R2311.1, R2312.1, U2301.3 (V+), U2301.8 (-); also elsewhere on the board

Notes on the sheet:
Non_Utilisé
Ouvvert
Court-circuit
